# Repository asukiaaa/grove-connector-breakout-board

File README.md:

# grove-connector-breakout-board

Breakout boards to use grove connector on a bread board.

## Setup

This project use submodule so execute this command after cloning.

```
git submodule update --init --recursive
```

## horizontal-both-sides

## horizontal-one-line

## vertical-both-sides

## vertical-one-line

## References

- [Groveコネクタをブレッドボードで使うためのブレイクアウトボードを作ってみた](https://asukiaaa.blogspot.com/2020/12/grove-connector-breakout.html)
- [Grove System](https://wiki.seeedstudio.com/Grove_System/)

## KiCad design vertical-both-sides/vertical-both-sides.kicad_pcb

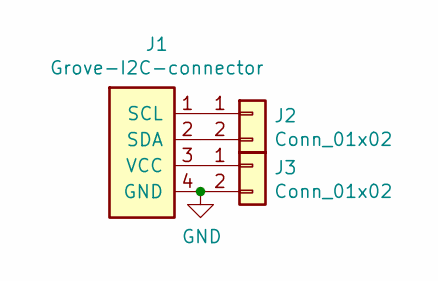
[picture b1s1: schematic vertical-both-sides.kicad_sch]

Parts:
J1: Grove-I2C-connector; NS-Tech_Grove_1x04_P2mm_Vertical_silk_inside
J2: Conn_01x02; PinHeader_1x02_P2.54mm_Vertical_silk_inside
J3: Conn_01x02; PinHeader_1x02_P2.54mm_Vertical_all_circle_silk_inside

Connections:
GND: J1.4 (GND), J3.2
unnamed: J1.1 (SCL), J2.1
unnamed: J1.2 (SDA), J2.2
unnamed: J1.3 (VCC), J3.1

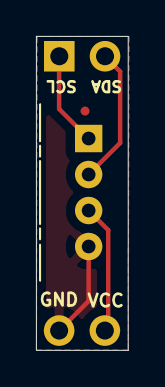
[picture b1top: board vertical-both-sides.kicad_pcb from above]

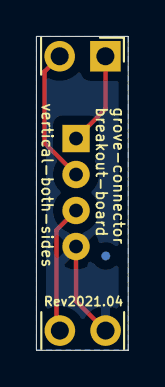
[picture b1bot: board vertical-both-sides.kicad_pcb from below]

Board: 2 copper layers, 5.1 x 17.4 mm, 5 parts (3 on the bottom side), 4 nets.

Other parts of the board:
Fid1, Fid2: Fiducial_0.5mm_Mask1mm

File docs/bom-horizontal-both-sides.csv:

"Ref","Qnty","Value","Cmp name","Footprint","Description","Vendor"
"J1","1","Grove-I2C-connector","Grove-I2C-connector","my-kicad-footprints:NS-Tech_Grove_1x04_P2mm_Horizontal_silk_inside","","https://www.seeedstudio.com/Grove-Universal-4-pin-connector-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"
"J2, J3","2","Conn_01x04","Conn_01x04","my-kicad-footprints:PinHeader_1x04_P2.54mm_Vertical_silk_inside","white","https://ja.aliexpress.com/item/4001111914708.html"

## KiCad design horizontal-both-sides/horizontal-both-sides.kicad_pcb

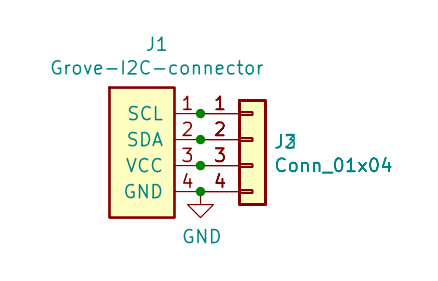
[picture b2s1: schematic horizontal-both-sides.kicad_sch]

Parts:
J1: Grove-I2C-connector; NS-Tech_Grove_1x04_P2mm_Horizontal_silk_inside
J2, J3: Conn_01x04; PinHeader_1x04_P2.54mm_Vertical_silk_inside

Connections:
GND: J1.4 (GND), J2.4, J3.4
unnamed: J1.1 (SCL), J2.1, J3.1
unnamed: J1.2 (SDA), J2.2, J3.2
unnamed: J1.3 (VCC), J2.3, J3.3

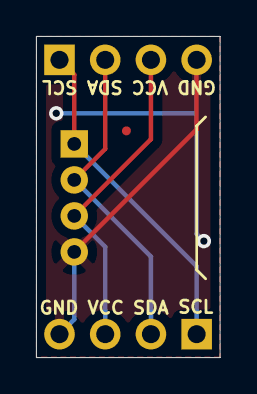
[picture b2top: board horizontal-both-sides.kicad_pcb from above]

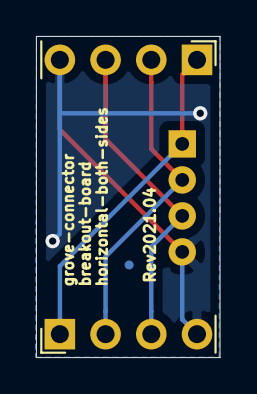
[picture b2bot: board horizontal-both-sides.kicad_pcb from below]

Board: 2 copper layers, 10.2 x 17.8 mm, 5 parts (3 on the bottom side), 4 nets.

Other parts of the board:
fid1, fid2: Fiducial_0.5mm_Mask1mm

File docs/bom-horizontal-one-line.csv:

"Ref","Qnty","Value","Cmp name","Footprint","Description","Vendor"
"J1","1","Grove-I2C-connector","Grove-I2C-connector","my-kicad-footprints:NS-Tech_Grove_1x04_P2mm_Horizontalnside_silk_i","","https://www.seeedstudio.com/Grove-Universal-4-pin-connector-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"
"J2","1","Conn_01x04","Conn_01x04","my-kicad-footprints:PinHeader_1x04_P2.54mm_Vertical_silk_inside","white","https://ja.aliexpress.com/item/4001111914708.html"

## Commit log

2020-11-25 Add arrows about size
2020-12-06 Correct typo on readme
2020-12-15 Add schematic and images
2021-04-06 Update revision for bertical botn and one line and horizontal both
2021-05-18 Adjust text thickness and position
2022-11-23 Add labels
2022-11-23 Update each projects for kicad6
2022-11-23 Add bom for each designs
